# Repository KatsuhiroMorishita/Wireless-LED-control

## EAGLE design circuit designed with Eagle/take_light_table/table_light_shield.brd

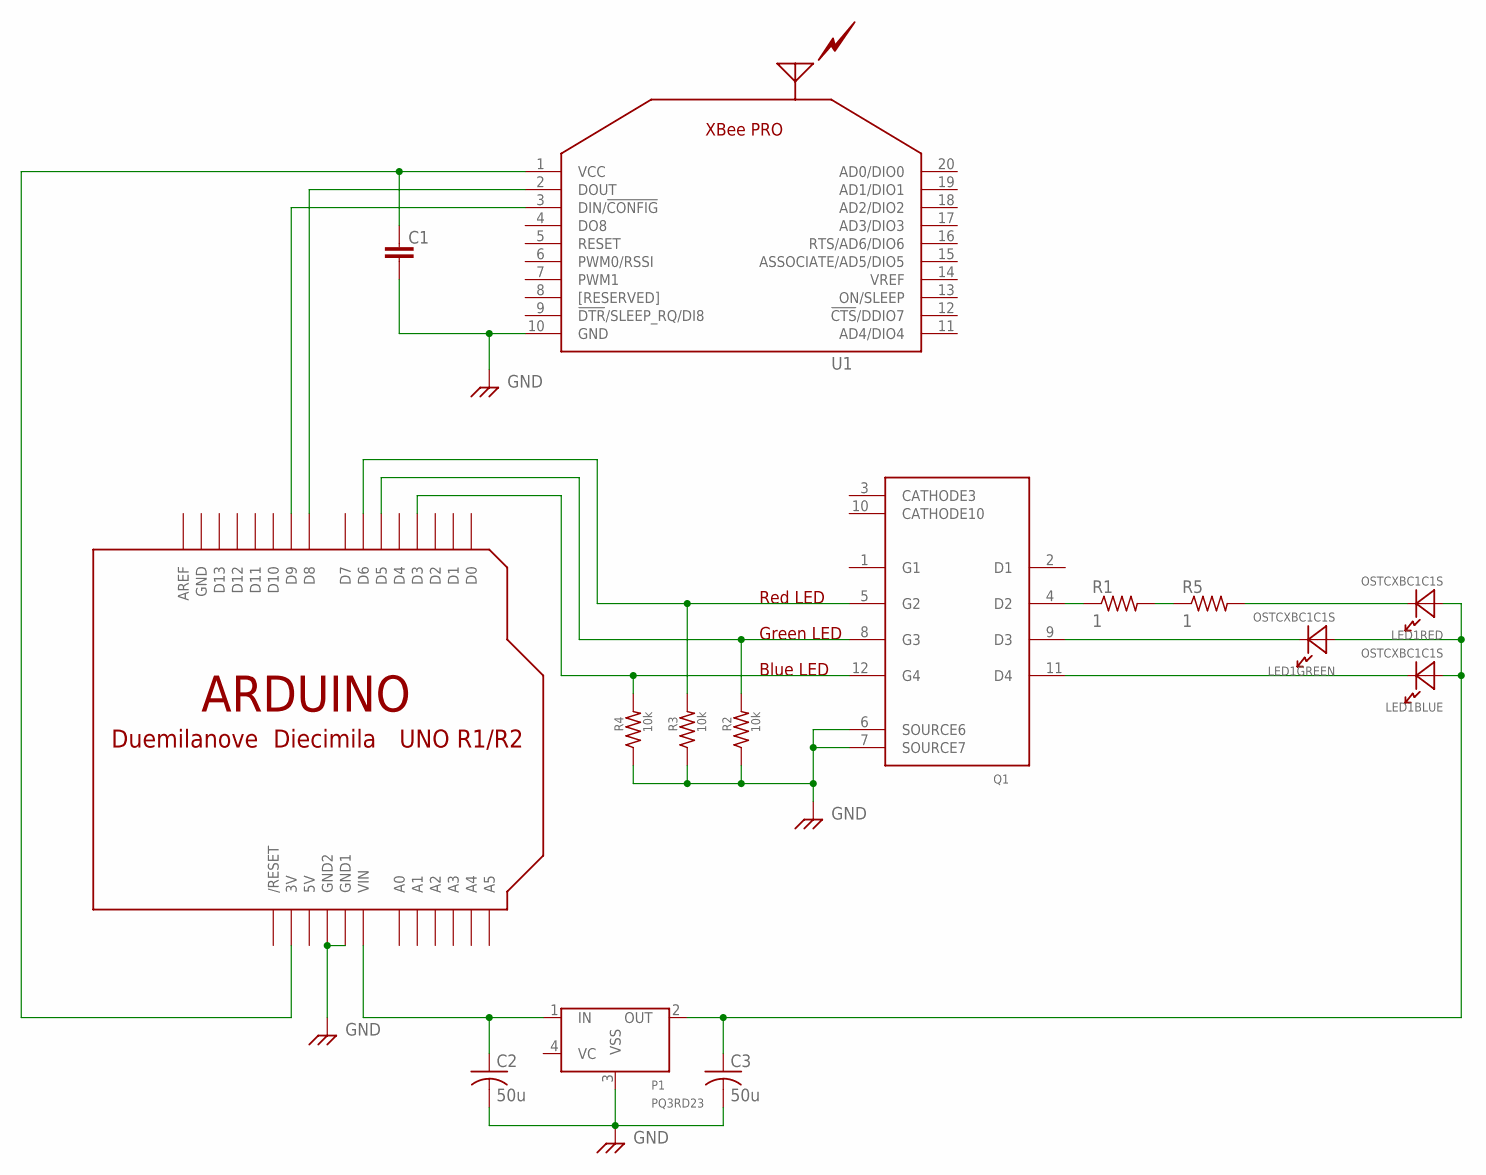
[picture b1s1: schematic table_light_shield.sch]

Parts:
C1: GRM18; 1608(1.6*0.8MM)
C2, C3: 50u; C025-050X050
LED1: OSTCXBC1C1S; OSTCXBC1C1S_WITH_HEATSINK
P1: PQ3RD23
Q1: MP4401
R1, R5: 1; 0805-THM
R2, R3, R4: 10k; 1608(1.6*0.8MM)
U1: XBEE_PROXPPN101BFCN; XBEE_ON_XPPN101BFCN-RC
U$1: ARDUINO-NOHOLE

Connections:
5V: U$1.5V
GND: C1.P$2 (2), C2.2, C3.2, P1.3 (VSS), Q1.6 (SOURCE6), Q1.7 (SOURCE7), R2.P$3 (1), R3.P$3 (1), R4.P$3 (1), U1.10 (GND), U$1.GND, U$1.GND1, U$1.GND2
unnamed: C2.1, P1.1 (IN), U$1.VIN
unnamed: Q1.4 (D2), R1.1
unnamed: Q1.5 (G2), R3.P$4 (2), U$1.D6
unnamed: Q1.8 (G3), R2.P$4 (2), U$1.D5
unnamed: Q1.12 (G4), R4.P$4 (2), U$1.D3
unnamed: C1.P$1 (1), U1.1 (VCC), U$1.3V
unnamed: U1.2 (DOUT), U$1.D8
unnamed: U1.3 (DIN/!CONFIG), U$1.D9
unnamed: LED1.B- (C), Q1.11 (D4)
unnamed: LED1.R- (C), R5.2
unnamed: R1.2, R5.1
unnamed: C3.1, LED1.B+ (A), LED1.G+ (A), LED1.R+ (A), P1.2 (OUT)
unnamed: LED1.G- (C), Q1.9 (D3)

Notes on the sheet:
Red LED
Green LED
Blue LED

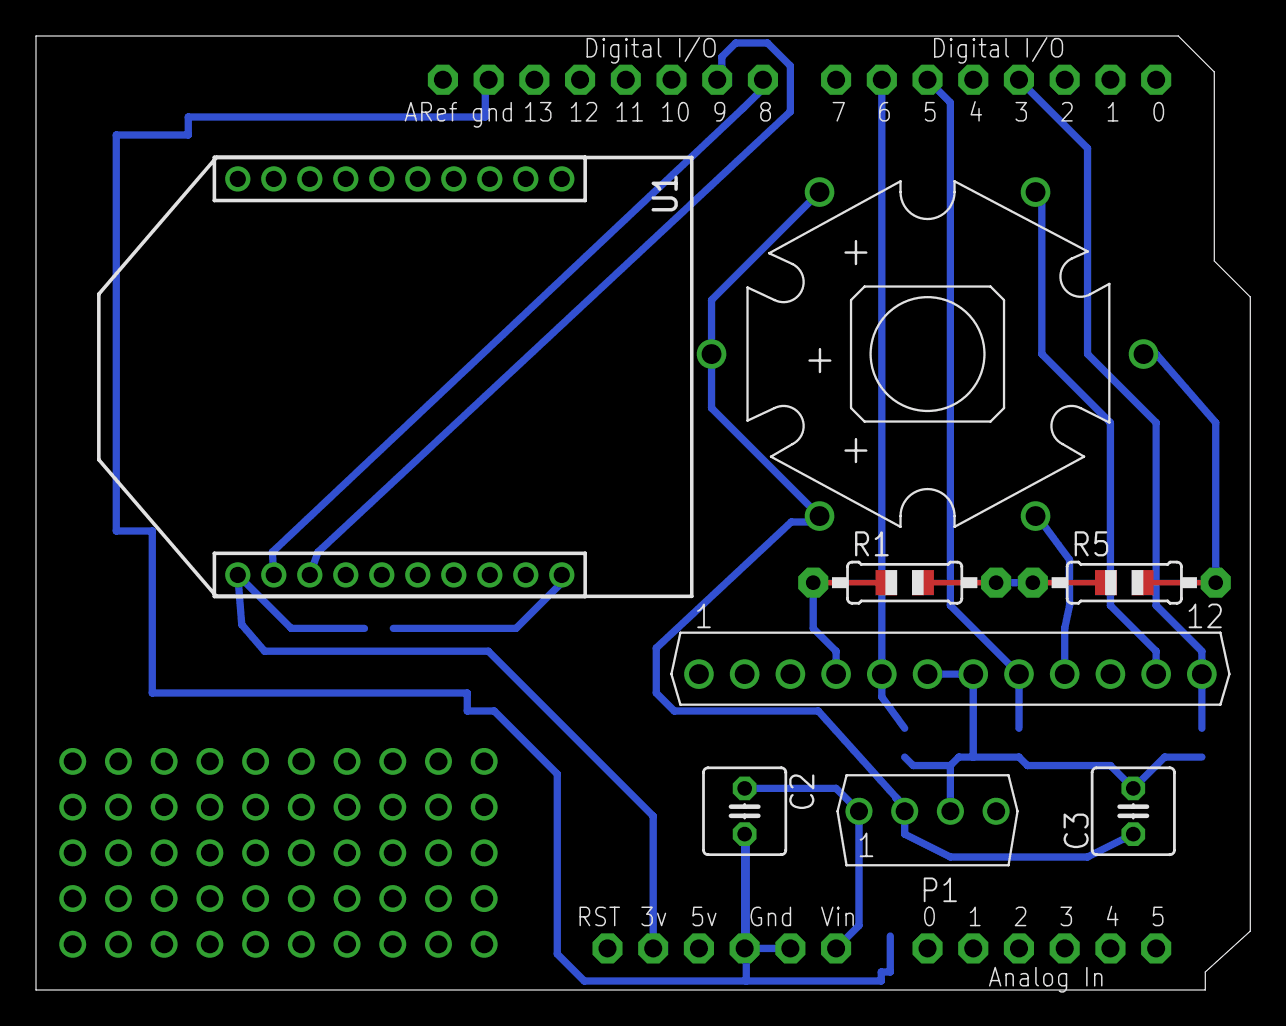
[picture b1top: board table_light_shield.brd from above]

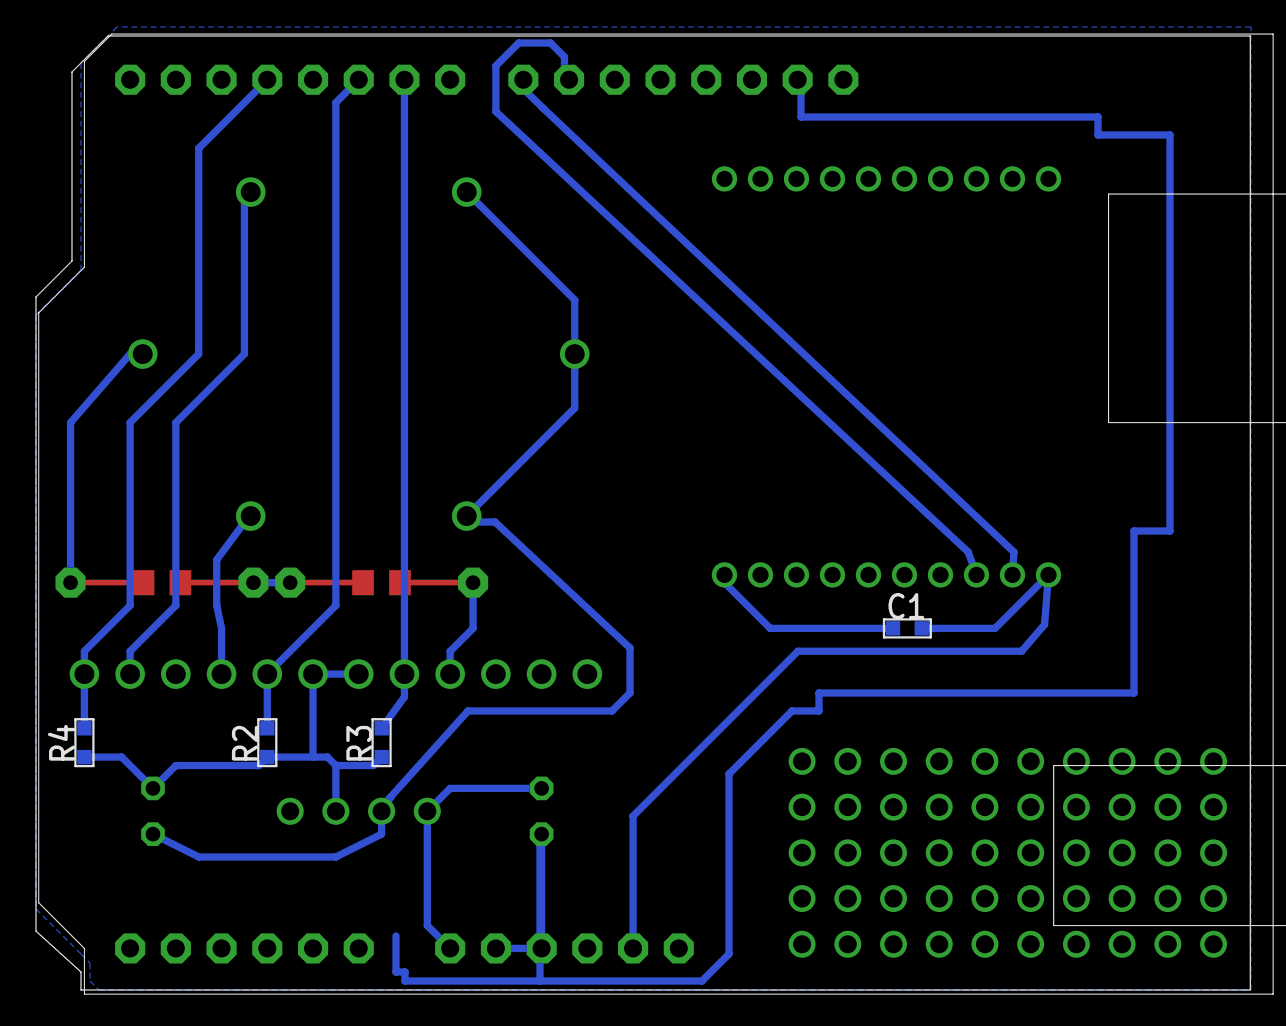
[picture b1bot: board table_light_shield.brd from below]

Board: 2 copper layers, 67.5 x 53.0 mm, 13 parts (4 on the bottom side), 14 nets.

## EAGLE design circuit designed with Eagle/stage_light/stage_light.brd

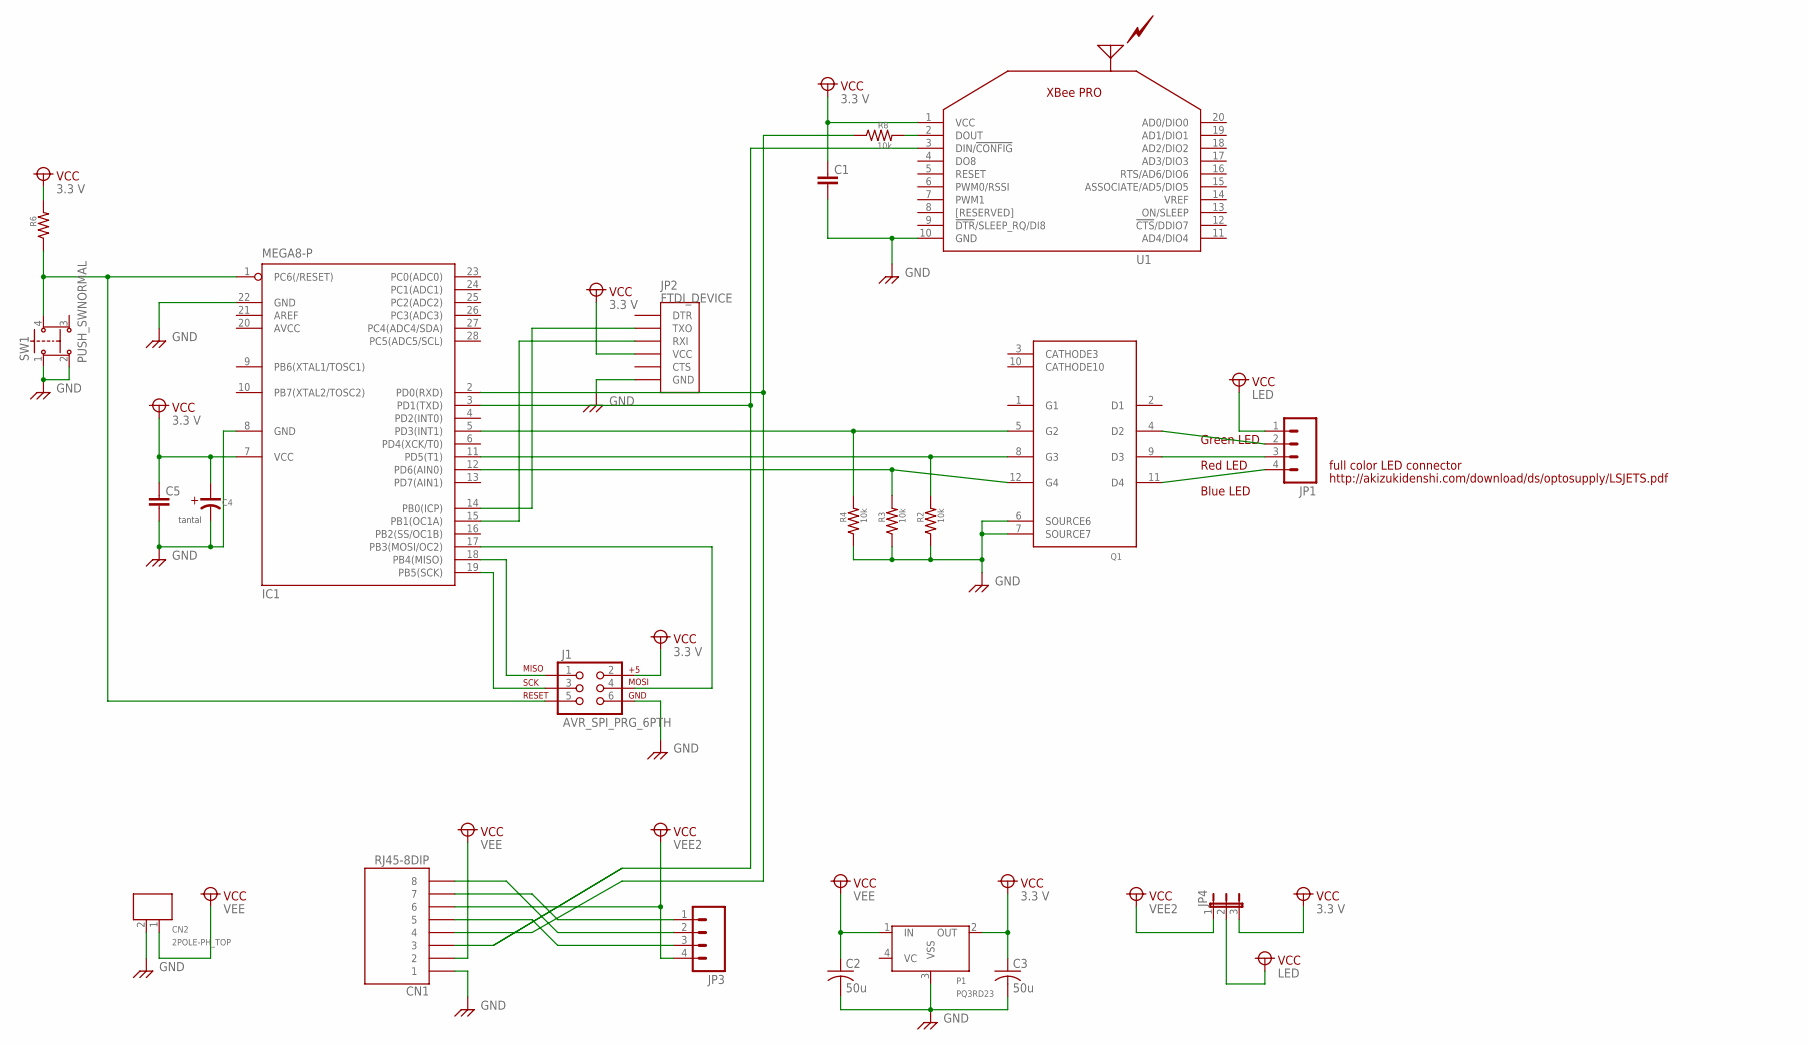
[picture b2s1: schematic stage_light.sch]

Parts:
C1, C5: GRM18; 1608(1.6*0.8MM)
C2, C3: 50u; C025-050X050
C4: CT-100U; 6134(6.1*3.4MM)_POLAR
CN1: RJ45-8DIP; AE-RJ-45-LAN-DIP-A
CN2: 2POLE-PH_TOP; B2B-PH-K-S(2MM_PITCH)
IC1: MEGA8-P; DIL28-3
J1: AVR_SPI_PRG_6PTH; 2X3
JP1: M04LONGPADS; 1X04_LONGPADS
JP2: FTDI_DEVICE; FTDI_DEVICE_SIDE
JP3: M04PTH; 1X04
JP4: JP2E; JP2
P1: PQ3RD23
Q1: MP4401
R2, R3, R4, R8: 10k; 1608(1.6*0.8MM)
R6: CHIP1608; 1608(1.6*0.8MM)
SW1: PUSH_SWNORMAL; PUSH_SW
U1: XBEE_PROXPPN101BFCN; XBEE_ON_XPPN101BFCN-RC

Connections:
AVCC: IC1.20 (AVCC)
GND: C1.P$2 (2), C2.2, C3.2, C4.-, C5.P$2 (2), CN1.1, CN2.2, IC1.8 (GND), IC1.22 (GND), J1.6, JP2.P$6 (GND), P1.3 (VSS), Q1.6 (SOURCE6), Q1.7 (SOURCE7), R2.P$3 (1), R3.P$3 (1), R4.P$3 (1), SW1.1, SW1.2, U1.10 (GND)
unnamed: JP1.3, Q1.9 (D3)
unnamed: JP1.2, Q1.4 (D2)
unnamed: IC1.12 (PD6(AIN0)), Q1.12 (G4), R3.P$4 (2)
unnamed: IC1.11 (PD5(T1)), Q1.8 (G3), R2.P$4 (2)
unnamed: IC1.5 (PD3(INT1)), Q1.5 (G2), R4.P$4 (2)
unnamed: JP1.4, Q1.11 (D4)
unnamed: IC1.14 (PB0(ICP)), JP2.P$2 (TXO)
unnamed: IC1.15 (PB1(OC1A)), JP2.P$3 (RXI)
unnamed: CN1.8, JP3.2
unnamed: CN1.5, JP3.3
unnamed: CN1.7, JP3.1
unnamed: IC1.1 (PC6(/RESET)), J1.5, R6.P$3 (1), SW1.4 (P3)
unnamed: R8.P$4 (2), U1.2 (DOUT)
unnamed: CN1.4, IC1.2 (PD0(RXD)), R8.P$3 (1)
unnamed: CN1.3, IC1.3 (PD1(TXD)), U1.3 (DIN/!CONFIG)
unnamed: IC1.18 (PB4(MISO)), J1.1
unnamed: IC1.19 (PB5(SCK)), J1.3
unnamed: IC1.17 (PB3(MOSI/OC2)), J1.4
VCC1: C2.1, CN1.2, CN2.1, P1.1 (IN)
VCC2: C1.P$1 (1), C3.1, C4.+, C5.P$1 (1), IC1.7 (VCC), J1.2, JP2.P$4 (VCC), JP4.3, P1.2 (OUT), R6.P$4 (2), U1.1 (VCC)
VCC3: JP1.1, JP4.2
VCC4: CN1.6, JP3.4, JP4.1

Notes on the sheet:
Red LED
Green LED
Blue LED
full color LED connector
http://akizukidenshi.com/download/ds/optosupply/LSJETS.pdf

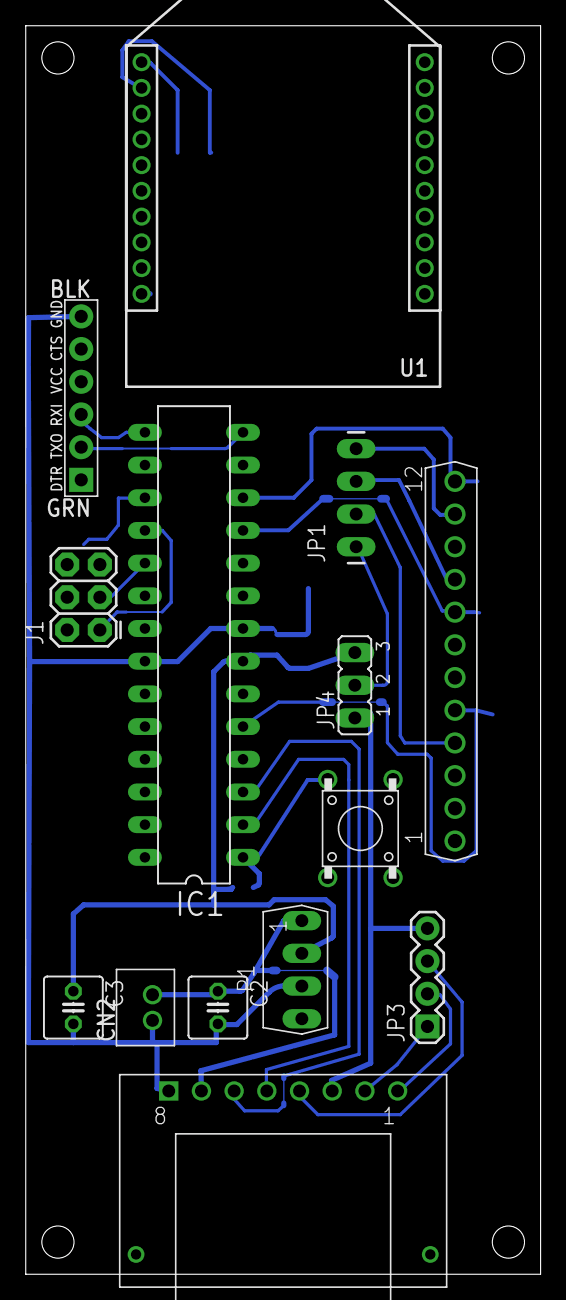
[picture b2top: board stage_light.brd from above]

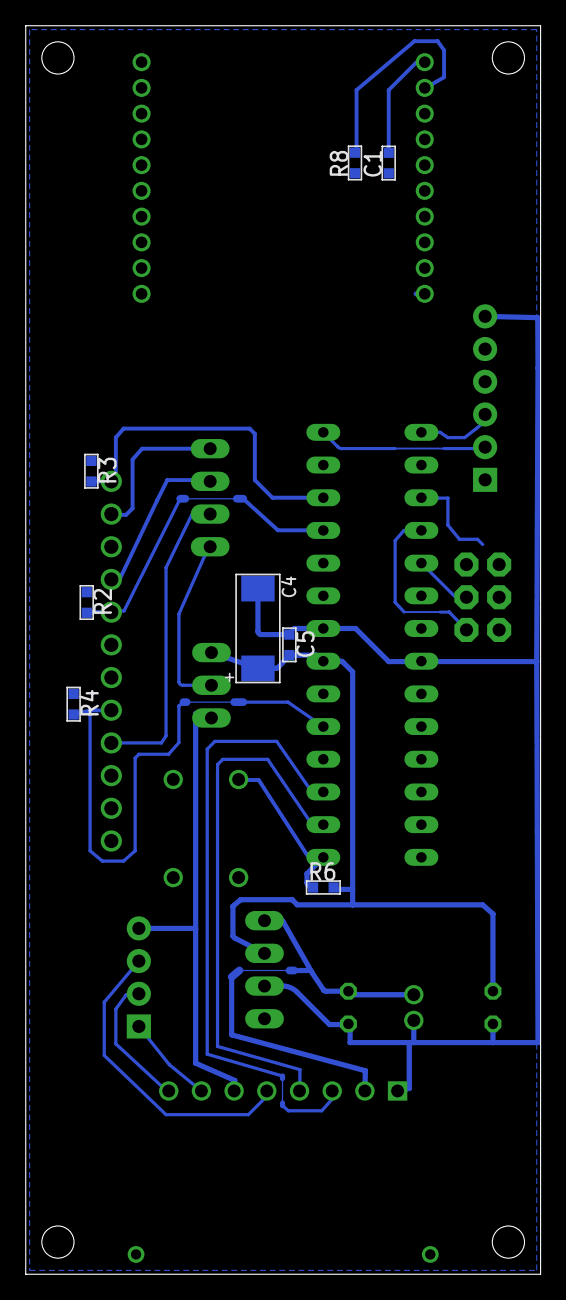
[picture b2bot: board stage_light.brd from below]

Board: 2 copper layers, 40.0 x 97.0 mm, 22 parts (8 on the bottom side), 23 nets.

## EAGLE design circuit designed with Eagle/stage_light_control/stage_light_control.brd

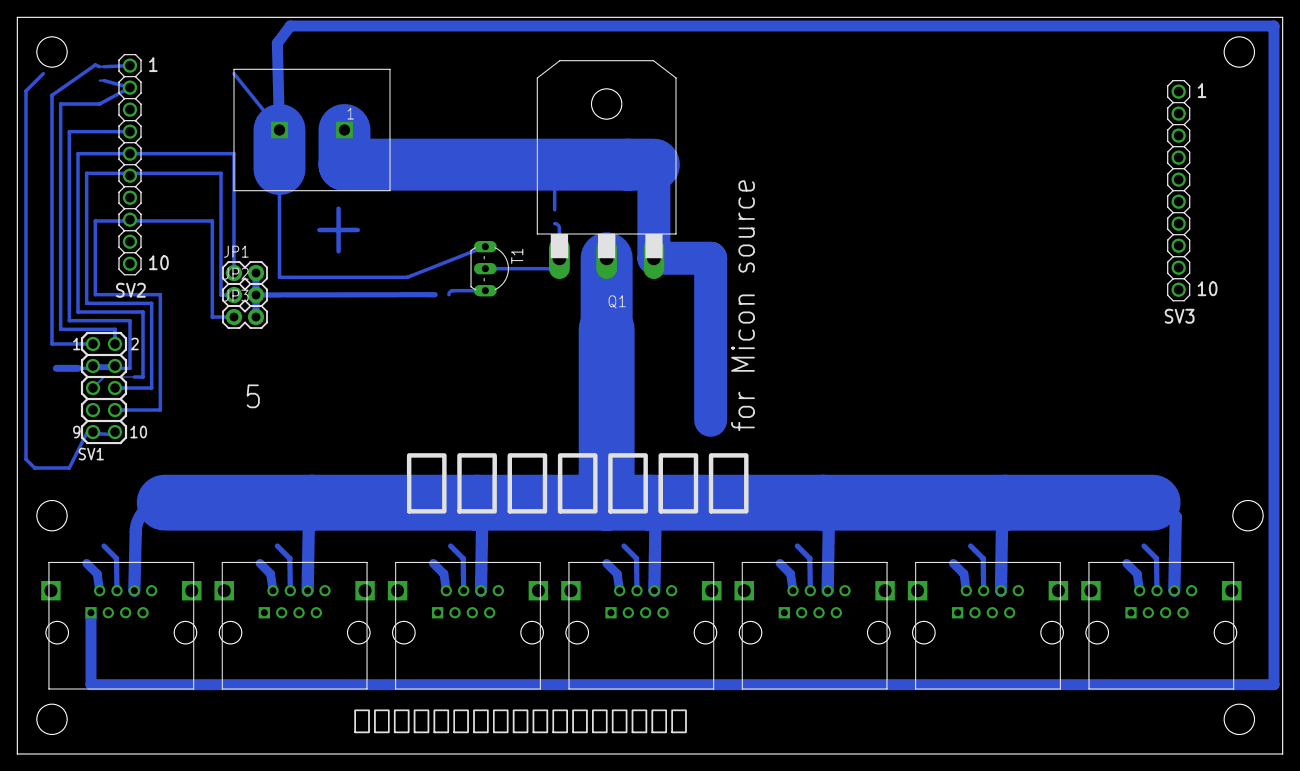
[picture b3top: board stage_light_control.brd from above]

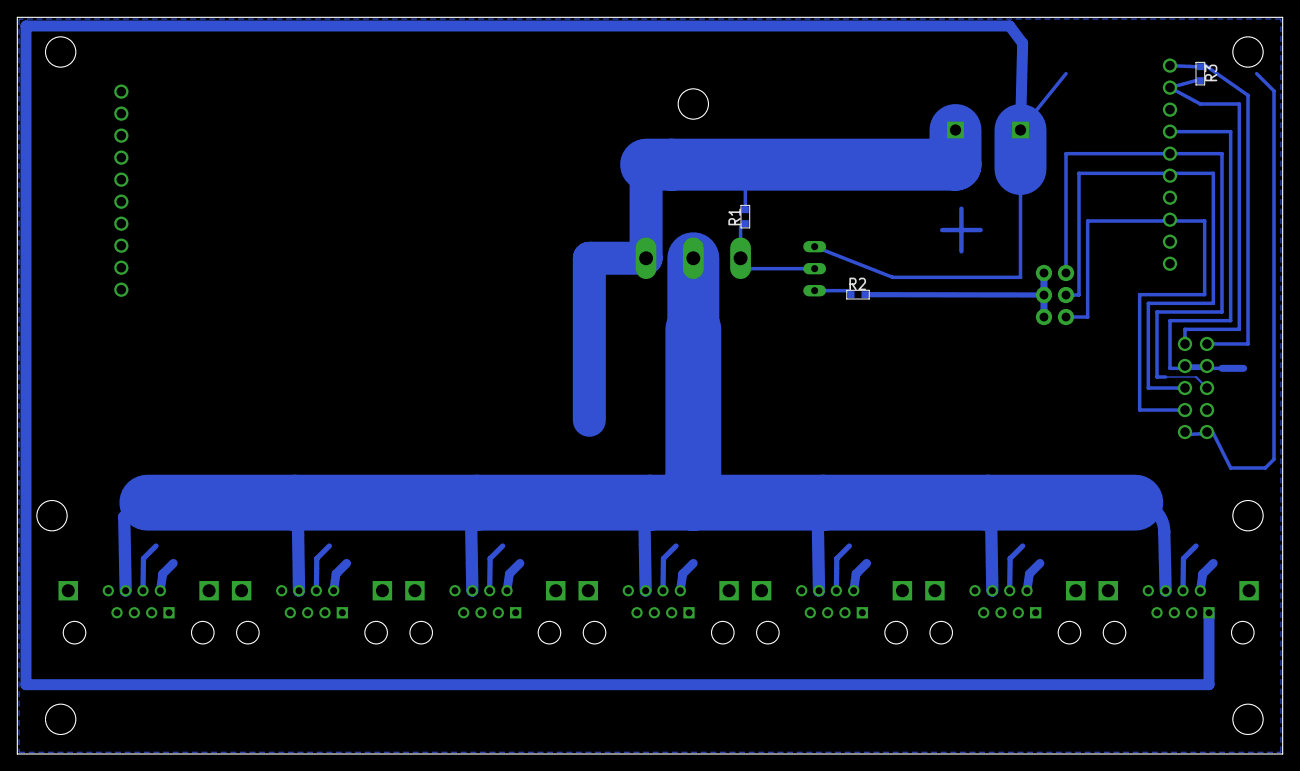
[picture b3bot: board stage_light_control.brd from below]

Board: 2 copper layers, 146.0 x 85.0 mm, 19 parts (3 on the bottom side), 12 nets.

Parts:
CN1, CN2, CN3, CN4, CN5, CN6, CN7: RJ45-8-7810; RJ-45_7810-8P8C
J1: 1X2-7.5MM
JP1, JP2, JP3: 1X02
Q1: 2SJ554-SIDEAY; TO-3P
R1: 2k; 1608(1.6*0.8MM)
R2, R3: 10k; 1608(1.6*0.8MM)
SV1: 10PIN-HEADER-DOUBLE_2.54PITCH; 2*5(2.54PITCH)
SV2, SV3: 10PIN-HEADERSINGLE_2.54PITCH; 1*10(2.54PITCH)
T1: 2SC1815; TO92-ECB

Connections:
GND: CN1.1, CN2.1, CN3.1, CN4.1, CN5.1, CN6.1, CN7.1, J1.P$2, SV1.10, SV2.10, T1.E
unnamed: Q1.1, R1.P$3, T1.C
unnamed: R2.P$3, T1.B
unnamed: JP1.1, SV1.5, SV2.5
unnamed: JP2.1, SV1.6, SV2.6
unnamed: JP3.1, SV1.8, SV2.8
unnamed: CN1.6, CN2.6, CN3.6, CN4.6, CN5.6, CN6.6, CN7.6, Q1.2
unnamed: JP1.2, JP2.2, JP3.2, R2.P$4
TAG1: CN1.4, CN2.4, CN3.4, CN4.4, CN5.4, CN6.4, CN7.4, SV1.3, SV1.4, SV2.4
TAG2: R3.P$4, SV1.2, SV2.2
VCC1: R3.P$3, SV1.1, SV2.1
VCC2: CN1.2, CN2.2, CN3.2, CN4.2, CN5.2, CN6.2, CN7.2, J1.P$1, Q1.3, R1.P$4

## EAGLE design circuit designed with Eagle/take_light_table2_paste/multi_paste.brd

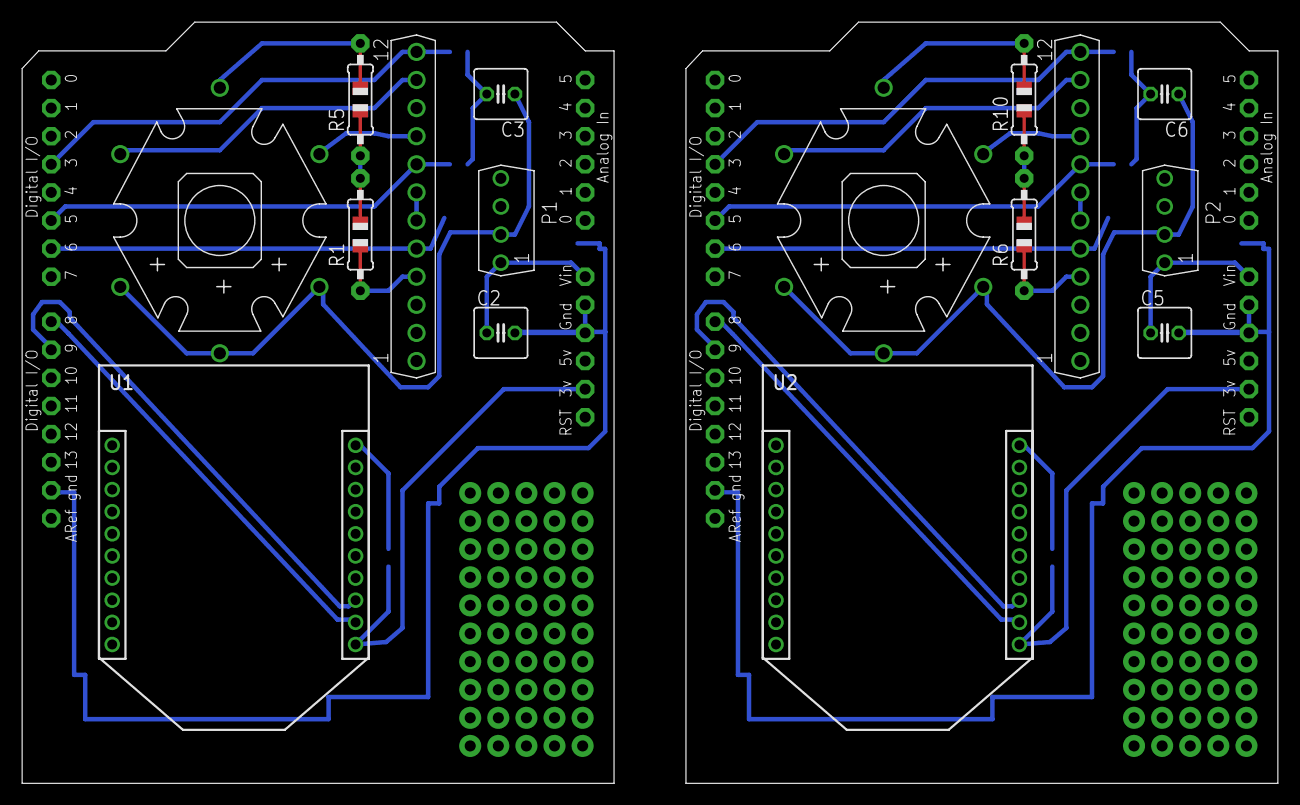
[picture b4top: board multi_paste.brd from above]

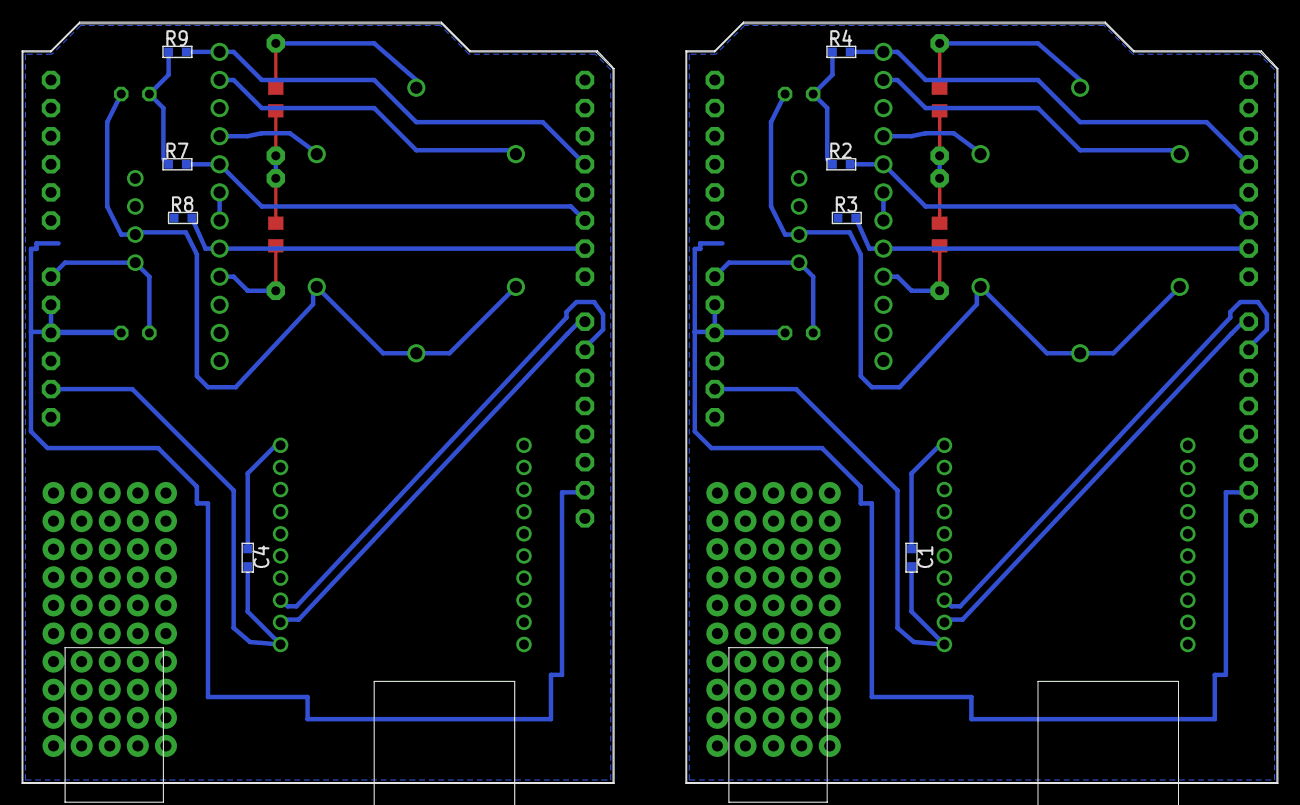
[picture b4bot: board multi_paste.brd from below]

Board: 2 copper layers, 113.5 x 68.8 mm, 26 parts (8 on the bottom side), 28 nets.

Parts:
C1, C4: 1608(1.6*0.8MM)
C2, C3, C5, C6: 50u; C025-050X050
LED1, LED2: OSTCXBC1C1S; OSTCXBC1C1S_WITH_HEATSINK
P1, P2: PQ3RD23
Q1, Q2: MP4401
R1, R5, R6, R10: 1; 0805-THM
R2, R3, R4, R7, R8, R9: 10k; 1608(1.6*0.8MM)
U1, U2: XBEE_PROXPPN101BFCN; XBEE_ON_XPPN101BFCN-RC
U$1, U$2: ARDUINO-NOHOLE

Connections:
GND: C1.P$2, C2.2, C3.2, P1.3, Q1.6, Q1.7, R2.P$3, R3.P$3, R4.P$3, U1.10, U$1.GND, U$1.GND1, U$1.GND2
GND1: C4.P$2, C5.2, C6.2, P2.3, Q2.6, Q2.7, R7.P$3, R8.P$3, R9.P$3, U2.10, U$2.GND, U$2.GND1, U$2.GND2
unnamed: C2.1, P1.1, U$1.VIN
unnamed: Q1.4, R1.1
unnamed: Q1.5, R3.P$4, U$1.D6
unnamed: Q1.8, R2.P$4, U$1.D5
unnamed: Q1.12, R4.P$4, U$1.D3
unnamed: C1.P$1, U1.1, U$1.3V
unnamed: U1.2, U$1.D8
unnamed: U1.3, U$1.D9
unnamed: LED1.B-, Q1.11
unnamed: LED1.R-, R5.2
unnamed: R1.2, R5.1
unnamed: C3.1, LED1.B+, LED1.G+, LED1.R+, P1.2
unnamed: LED1.G-, Q1.9
unnamed: C5.1, P2.1, U$2.VIN
unnamed: Q2.4, R6.1
unnamed: Q2.5, R8.P$4, U$2.D6
unnamed: Q2.8, R7.P$4, U$2.D5
unnamed: Q2.12, R9.P$4, U$2.D3
unnamed: C4.P$1, U2.1, U$2.3V
unnamed: U2.2, U$2.D8
unnamed: U2.3, U$2.D9
unnamed: LED2.B-, Q2.11
unnamed: LED2.R-, R10.2
unnamed: C6.1, LED2.B+, LED2.G+, LED2.R+, P2.2
unnamed: LED2.G-, Q2.9
unnamed: R6.2, R10.1

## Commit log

2014-05-07 初めてのコミット
2014-05-25 v3の追加
    新しいプロトコルに対応したv3を追加しました。v3はIDの書き換えとEEPROMへのバックアップに対応しています。まだ動作テストは実施していませ
    ん。
2014-05-29 正式版のプロトコルに対応
    アドレス処理に関するテストを行っていない。なお、リアルタイムでFFTを実施して発色を変化させるサンプルを追加した。
2014-05-30 FFT結果表示におけるバグ修正
    テーブル向けのprocessingスケッチについて、FFTの結果を棒グラフで表示できていなかったバグを修正した。また、電子回路の設計に関するメモ
    を追加している。
2014-05-30 hoge
    hoge
2014-05-30 ステージ上のLEDのためのスケッチ開発準備
    ステージ上のLEDを制御するためのスケッチをアップする準備です。電子回路の設計メモや回路モデルの資料も用意し始めました。スケッチはまだダミーです
    。
2014-05-30 字面を揃えた
    数字が並ぶように書き換えた。
2014-05-31 add comment
    コメントを追加
2014-05-31 EEPROMへIDを書き込む際と読み込む際にパリティをチェエクする機能を追加
    Arduinoに対してプログラムを書き込むとEEPROM内に書き込んだ内容がめちゃくちゃになっていたため、EEPROMから読みだしたデータのチェ
    ックを行う機能を追加した。
    実機でのテストは未実施なので注意のこと。
2014-06-02 プロトコル仕様が反映されていない抜けを埋めた
    プロトコルの仕様上はヘッダー以外で8 bit目が1（1000 0000）になることはないのだが、動いてしまった。したがって、そのバグを潰した。
2014-06-02 コメント修正
    コメントを修正した。あと、表示するメッセージも１箇所見なおした。
2014-06-02 新たに作ったバグを修正
    プロトコルを再チェックして、バグを修正しました。
2014-06-05 プロトコルの拡張
    ヘッダのバージョンを増やした。２つのプロトコルをストリーム内で混ぜなければ問題は生じない。
    XBeeとの通信速度を9600 bpsから19200 bpsへ変更した。40個のノードをほぼ10
    fpsで変更することが可能となった。通信速度はもう少し早くしても問題ないかもしれない。それよりも、色味の調整が大変な気がする。
2014-06-05 フォルダとファイル名の変更
    フォルダとファイル名を変更した。なお、v4は崇城大学の和泉先生による改造がなされている。
2014-06-05 コメントの変更
    コメントの変更した。また、ファイル名を再度変更した。ネーミングが悪かったかもしれない。
2014-06-06 高速ソフトシリアルAltSoftSerialへの対応
    高速ソフトシリアルAltSoftSerialへ対応した。これでXBeeとの通信速度19200
    bpsでデータ受信ロスはほぼ心配ないレベルとなった。また、制御用のProcessingサンプルスケッチを作成した。
2014-06-06 コメントを修正
    コメントを修正した。
2014-06-10 USBシリアルの自動検索に対応
    マシンに接続しているUSBシリアルポートが1つであることを前提に、自動的にシリアルポートを選択する機能を追加しました。
2014-06-12 スイッチ用スケッチを追加
    多数のユニットを制御するために、megaを用いたスイッチ制御を行うスケッチを追加した。これで1つのXBee当たりの制御対象LED発光ユニットを最
    大12個まで制御する。
    また、有線で接続されたモジュール様に、そちらは特に気にしない。
2014-06-13 ID割り振り直し
    和泉先生に正式なID割り振りを頂いたので、コード内のID割り振りをやり直した。
2014-06-23 本番時の電子回路や制御プログラムの保存
    2014-06-22時点での状況を保存します。
2014-06-23 CNC加工情報を追加
    CNCによる基板加工に利用した情報を追加しました。
2014-06-23 電子回路設計情報を整理
    見やすく整理しました。
2014-06-23 ステージ動作用のプログラムの説明を追加
    ステージ用のプログラムの動作条件等を追記しました。
2014-06-28 ステージ用のテープLED制御に対する様々な対応
    テストコードの追加や、配色配線への対応などを実施しました。内臓RC8
    MHzを利用するユーズ設定も加えています。また、通信路がうまく働くことを確認するために利用したPythonスクリプトも追加しています。
2015-04-29 プログラムの整理
    新しいモジュール用のコードも追加した。Type01に関してはなぜかバグっていたので修正した。
2015-04-30 type3用のサンプルコードをリポジトリに追加
    した
2015-04-30 type3のチラツキが収まらないので試行錯誤
    なんともならない・・・
2015-05-04 試験のために、係数を書き換えた
    indexの範囲などを変更している。
2015-05-04 ファイル名変更
    processingのプログラム名を書き換えた
2015-05-05 type01_firmwareを変更する前にコミット
    type01_firmwareを変更する前にコミットしました。ファイル名の整理や、コードの整理を多分に実施しています。
2015-05-06 自律制御・遠隔操作切り替えの実装
    自律制御・遠隔操作切り替え処理を実装した。また、コメントも見直した。
2015-05-06 processingのコードを整理
    processingのコードを整理して、キー入力での操作を行いやすくした。
2015-05-06 processingのコードを整理して、header2に関して1つにまとめた
    いままで1つのIDを対象としたものやキーボード入力とそうでないので分けていたが、意味が無いので1つにした。
2015-05-06 AD変換してシリアル出力するだけのコードを追加
    光センサをPCに接続するためだけのコード
2015-05-07 超音波センサのコードを追加
    遠隔操作モードへの切り替えが悪い。また、Type01の最新コードだと機能が切り替わっていないような気がする。
2015-09-27 ID書き換えコードの修正＆花畑スクランブル対応
    IDの書き換えが環境によって上手く行ったり行かなかったりする問題を修正した。また、2015-09-23の花畑スクランブルイベント「たまいれ」に向
    けたコードも追加した。
2015-10-05 名前と中身が入れ替わっていたのを修正
    ファイルを整理するときに間違えて名前をあべこべにつけていたらしい。
2015-10-28 温度で色を変えるコントローラーを文化祭で使うことになった
    2014年12月に東京国際フォーラムで使ったプログラムを若干変更して対応した。
2016-02-27 2016-02-28水前寺公園こいあかりマイコン制御スケッチを追加
2016-02-27 コメントを追加した

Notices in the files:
parts and their libraries:
SparkFun-Connectors: Licensing: Creative Commons ShareAlike 4.0 International - https://creativecommons.org/licenses/by-sa/4.0
